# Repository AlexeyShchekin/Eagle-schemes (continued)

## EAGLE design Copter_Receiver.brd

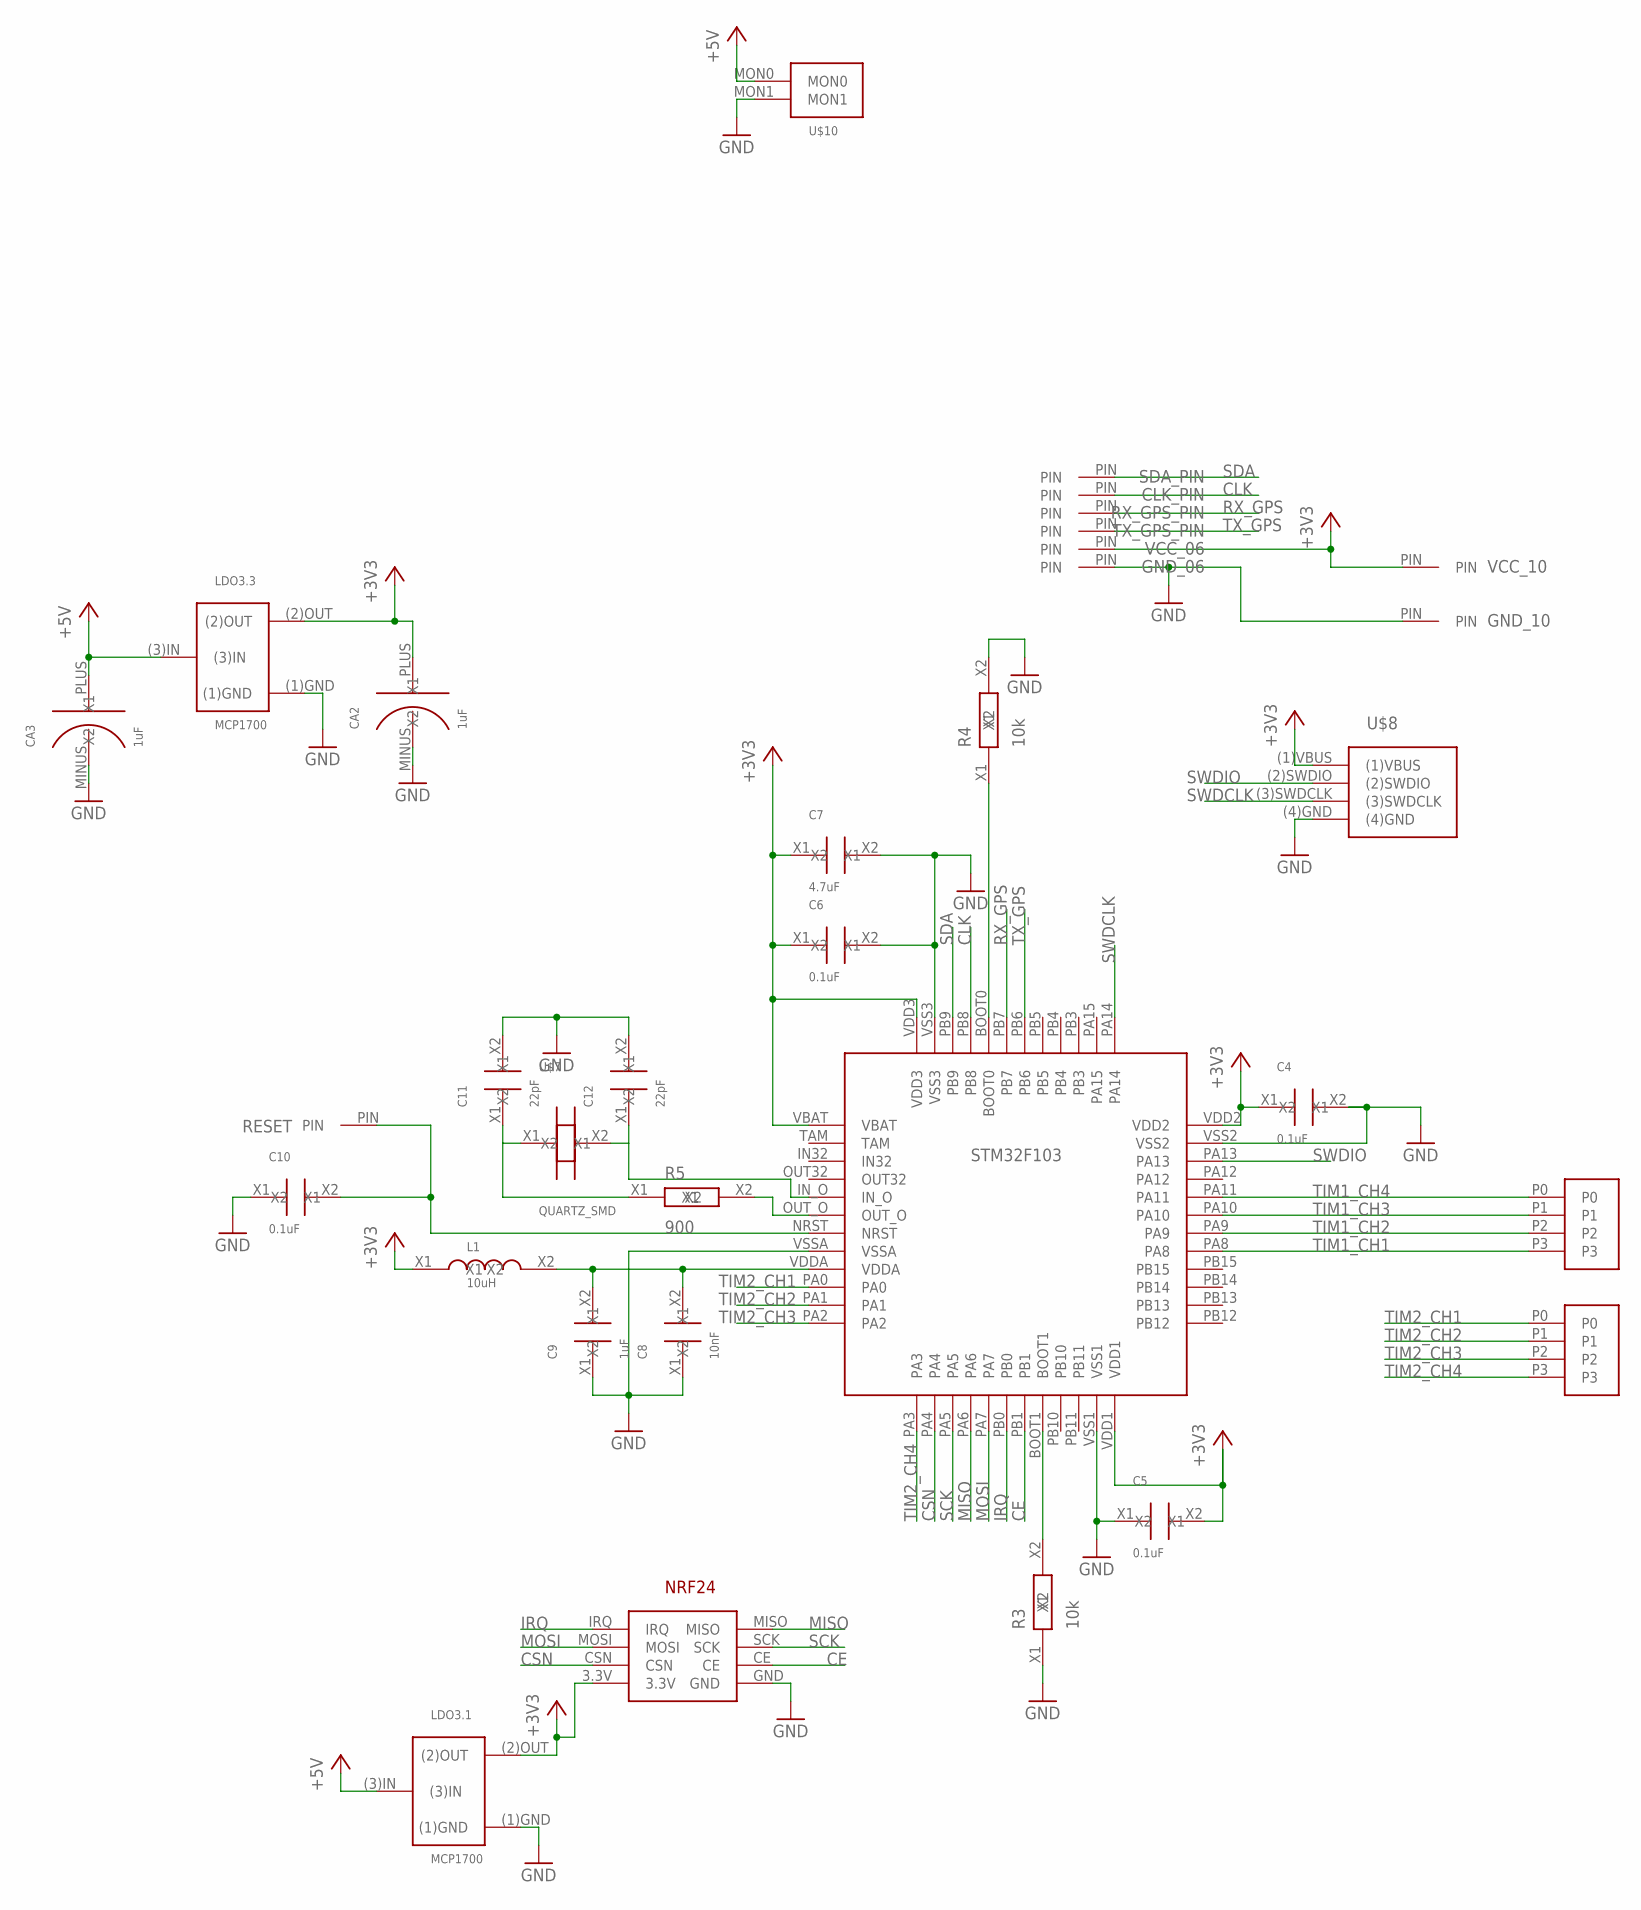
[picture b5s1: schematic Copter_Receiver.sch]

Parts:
C4, C5, C6, C10: 0.1uF; SMD_2.1X1.25
C7: 4.7uF; SMD_2.1X1.25
C8: 10nF; SMD_2.1X1.25
C9: 1uF; SMD_2.1X1.25
C11, C12: 22pF; SMD_2.1X1.25
CA2, CA3: 1uF; C_SMD_TA_A
CLK_PIN: PIN_06
GND_06: PIN_06
GND_10: PIN
L1: 10uH; SMD_2.1X1.25
LDO3.1, LDO3.3: MCP1700
R3, R4: 10k; SMD_2.1X1.25
R5: 900; SMD_2.1X1.25
RESET: PIN
RX_GPS_PIN: PIN_06
SDA_PIN: PIN_06
STM32F103: STM32F103CBT6
TX_GPS_PIN: PIN_06
U$1, U$3: 4PIN
U$2: NRF24_PLUG
U$7: QUARTZ_SMD
U$8: SWD
U$10: MON2PIN
VCC_06: PIN_06
VCC_10: PIN

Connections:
+3V3: C4.X1, C5.X2, C6.X1, C7.X1, CA2.PLUS (X2), L1.X1, LDO3.1.(2)OUT, LDO3.3.(2)OUT, STM32F103.VBAT, STM32F103.VDD1, STM32F103.VDD2, STM32F103.VDD3, U$2.3.3V, U$8.(1)VBUS, VCC_06.PIN, VCC_10.PIN
+5V: CA3.PLUS (X2), LDO3.1.(3)IN, LDO3.3.(3)IN, U$10.MON0
CE: STM32F103.PB1, U$2.CE
CLK: CLK_PIN.PIN, STM32F103.PB8
CSN: STM32F103.PA4, U$2.CSN
GND: C4.X2, C5.X1, C6.X2, C7.X2, C8.X1, C9.X1, C10.X1, C11.X2, C12.X2, CA2.MINUS (X1), CA3.MINUS (X1), GND_06.PIN, GND_10.PIN, LDO3.1.(1)GND, LDO3.3.(1)GND, R3.X1, R4.X2, STM32F103.VSS1, STM32F103.VSS2, STM32F103.VSS3, STM32F103.VSSA, U$2.GND, U$8.(4)GND, U$10.MON1
IRQ: STM32F103.PB0, U$2.IRQ
MISO: STM32F103.PA6, U$2.MISO
MOSI: STM32F103.PA7, U$2.MOSI
unnamed: R3.X2, STM32F103.BOOT1
unnamed: R4.X1, STM32F103.BOOT0
unnamed: R5.X2, STM32F103.OUT_O
unnamed: C11.X1, R5.X1, U$7.X1
unnamed: C12.X1, STM32F103.IN_O, U$7.X2
unnamed: C8.X2, C9.X2, L1.X2, STM32F103.VDDA
unnamed: C10.X2, RESET.PIN, STM32F103.NRST
RX_GPS: RX_GPS_PIN.PIN, STM32F103.PB7
SCK: STM32F103.PA5, U$2.SCK
SDA: SDA_PIN.PIN, STM32F103.PB9
SWDCLK: STM32F103.PA14, U$8.(3)SWDCLK
SWDIO: STM32F103.PA13, U$8.(2)SWDIO
TIM1_CH1: STM32F103.PA8, U$1.P3
TIM1_CH2: STM32F103.PA9, U$1.P2
TIM1_CH3: STM32F103.PA10, U$1.P1
TIM1_CH4: STM32F103.PA11, U$1.P0
TIM2_CH1: STM32F103.PA0, U$3.P0
TIM2_CH2: STM32F103.PA1, U$3.P1
TIM2_CH3: STM32F103.PA2, U$3.P2
TIM2_CH4: STM32F103.PA3, U$3.P3
TX_GPS: STM32F103.PB6, TX_GPS_PIN.PIN

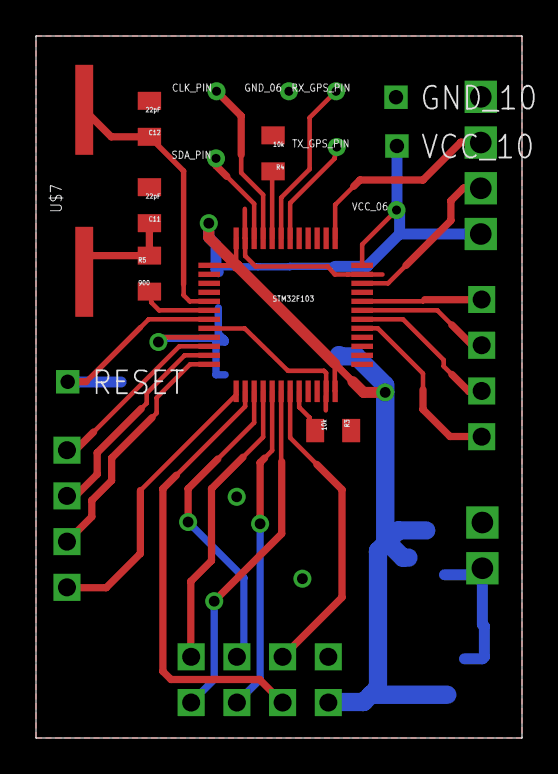
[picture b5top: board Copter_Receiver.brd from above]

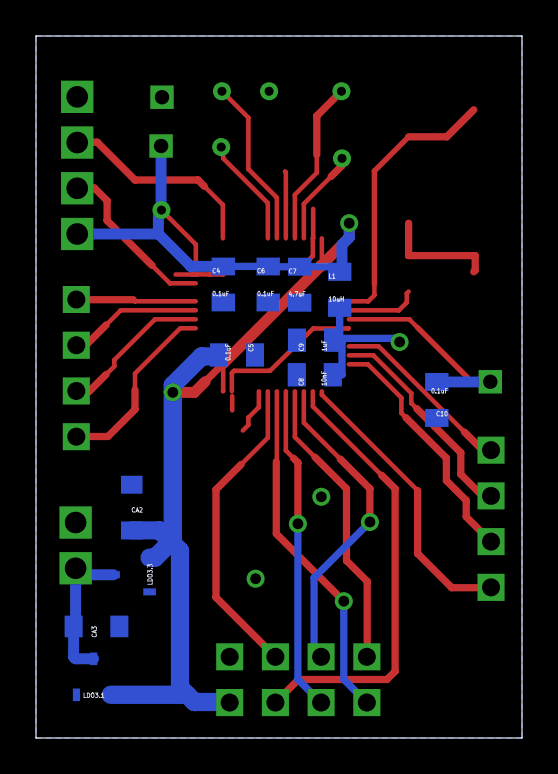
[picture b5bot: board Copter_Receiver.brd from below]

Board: 2 copper layers, 27.0 x 39.0 mm, 33 parts (12 on the bottom side), 30 nets.

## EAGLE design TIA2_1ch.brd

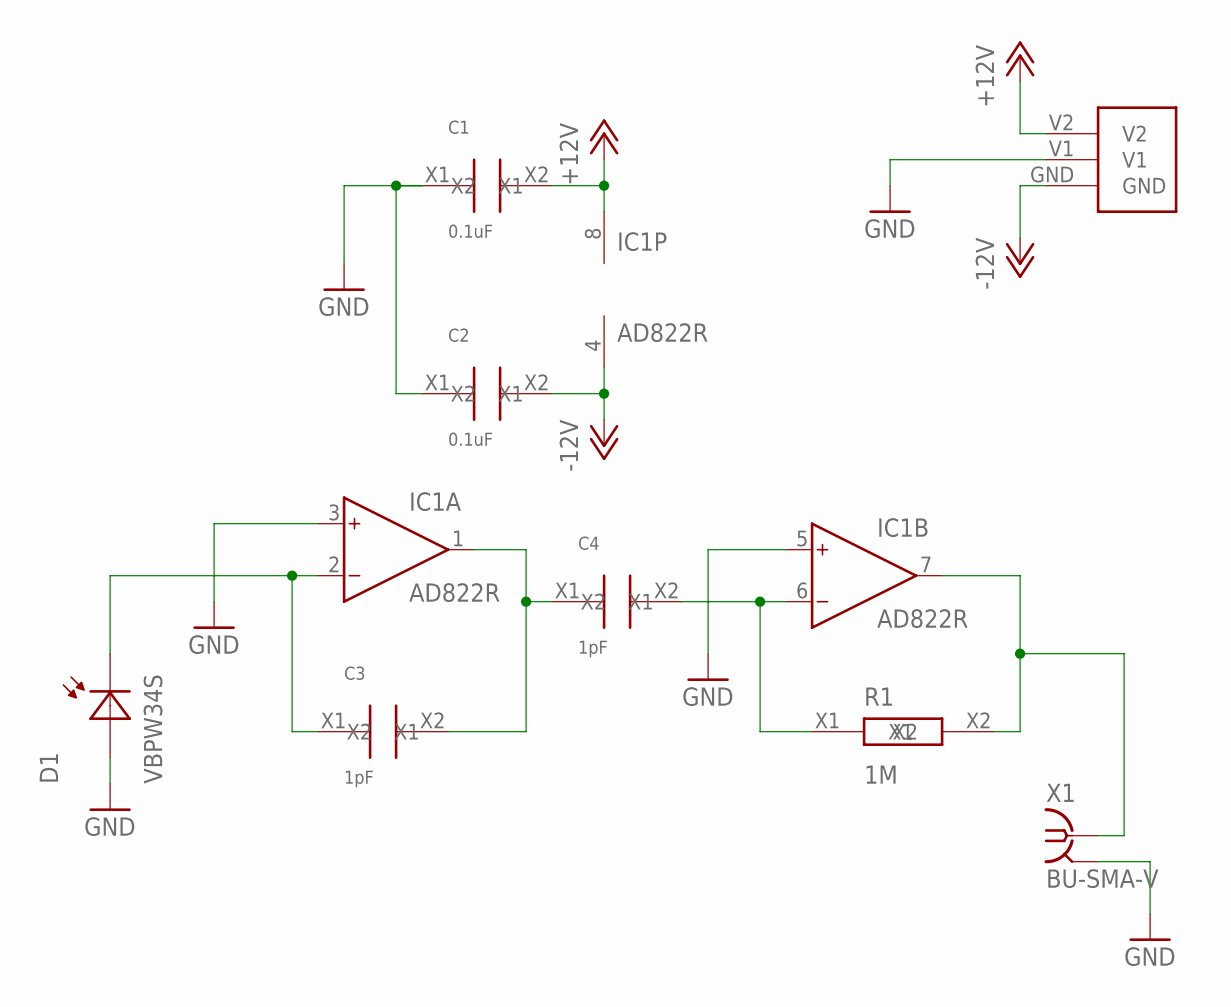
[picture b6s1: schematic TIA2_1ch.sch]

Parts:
C1, C2: 0.1uF; SMD_2.1X1.25
C3, C4: 1pF; SMD_2.1X1.25
D1: VBPW34S; SOD6439X130N
IC1: AD822R; SO8
R1: 1M; SMD_2.1X1.25
U$1: BAT3_PLUG
X1: BU-SMA-V

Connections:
+12V: C1.X2, IC1.8 (V+), U$1.V2
-12V: C2.X2, IC1.4 (V-), U$1.GND
GND: C1.X1, C2.X1, D1.A, IC1.3 (IN+), IC1.5 (IN+), U$1.V1, X1.2, X1.3 (2), X1.4 (2), X1.5 (2)
unnamed: C3.X1, D1.C, IC1.2 (IN-)
unnamed: C3.X2, C4.X1, IC1.1 (OUT)
unnamed: C4.X2, IC1.6 (IN-), R1.X1
unnamed: IC1.7 (OUT), R1.X2, X1.1

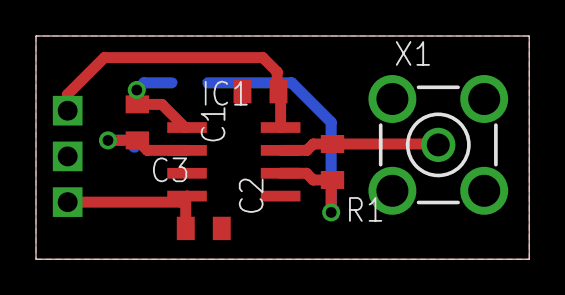
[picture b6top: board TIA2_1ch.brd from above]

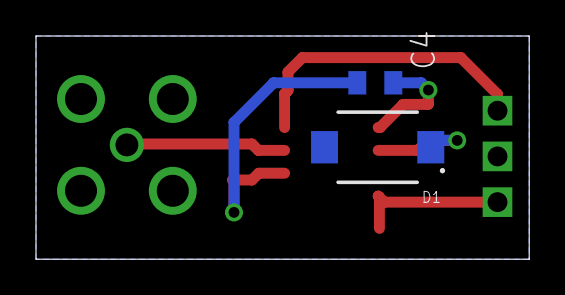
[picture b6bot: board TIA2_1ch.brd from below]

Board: 2 copper layers, 27.4 x 12.4 mm, 9 parts (2 on the bottom side), 7 nets.

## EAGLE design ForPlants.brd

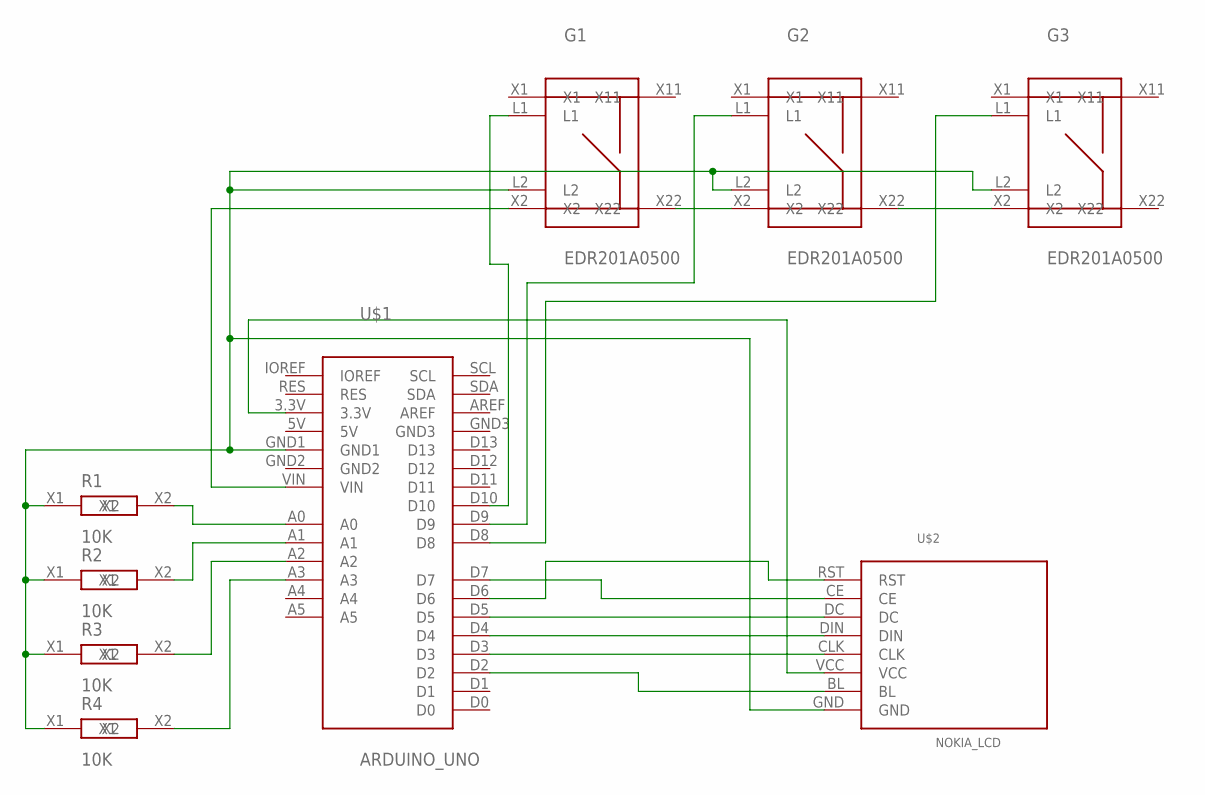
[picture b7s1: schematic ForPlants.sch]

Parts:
G1, G2, G3: EDR201A0500
R1, R2, R3, R4: 10K; SMD_2.1X1.25
U$1: ARDUINO_UNO
U$2: NOKIA_LCD

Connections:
unnamed: U$1.D7, U$2.CE
unnamed: U$1.D6, U$2.RST
unnamed: U$1.D5, U$2.DC
unnamed: U$1.D4, U$2.DIN
unnamed: U$1.D3, U$2.CLK
unnamed: U$1.D2, U$2.BL
unnamed: U$1.3.3V, U$2.VCC
unnamed: R1.X2, U$1.A0
unnamed: R2.X2, U$1.A1
unnamed: R3.X2, U$1.A2
unnamed: R4.X2, U$1.A3
unnamed: G1.L2, G2.L2, G3.L2, R1.X1, R2.X1, R3.X1, R4.X1, U$1.GND1, U$2.GND
unnamed: G1.X2, U$1.VIN
unnamed: G1.X22, G2.X2
unnamed: G2.X22, G3.X2
unnamed: G1.L1, U$1.D10
unnamed: G2.L1, U$1.D9
unnamed: G3.L1, U$1.D8

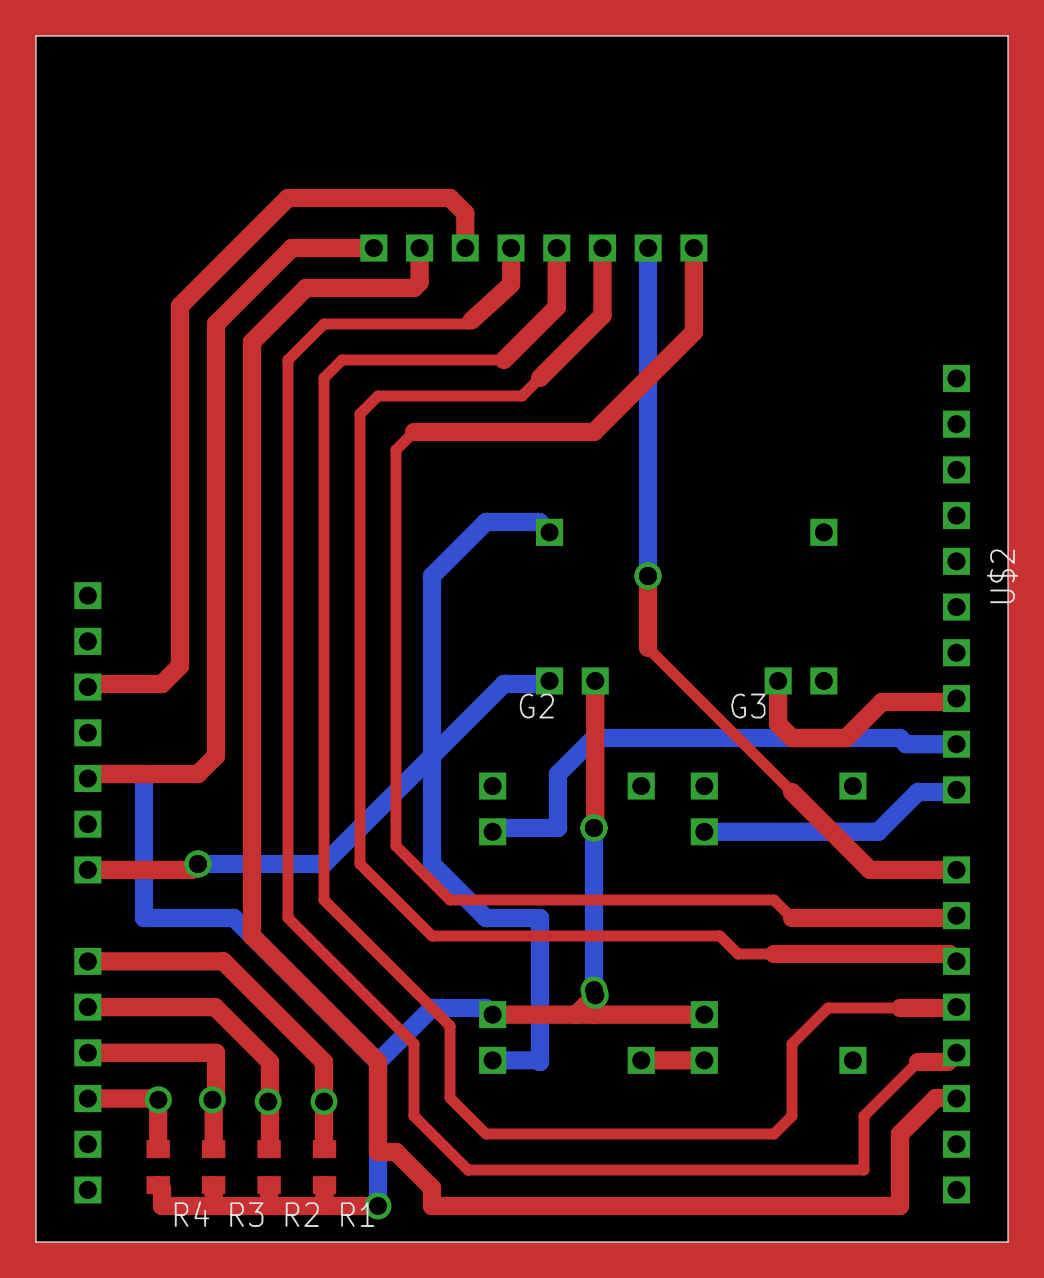
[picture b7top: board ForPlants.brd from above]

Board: 2 copper layers, 54.0 x 67.0 mm, 9 parts (1 on the bottom side), 18 nets.

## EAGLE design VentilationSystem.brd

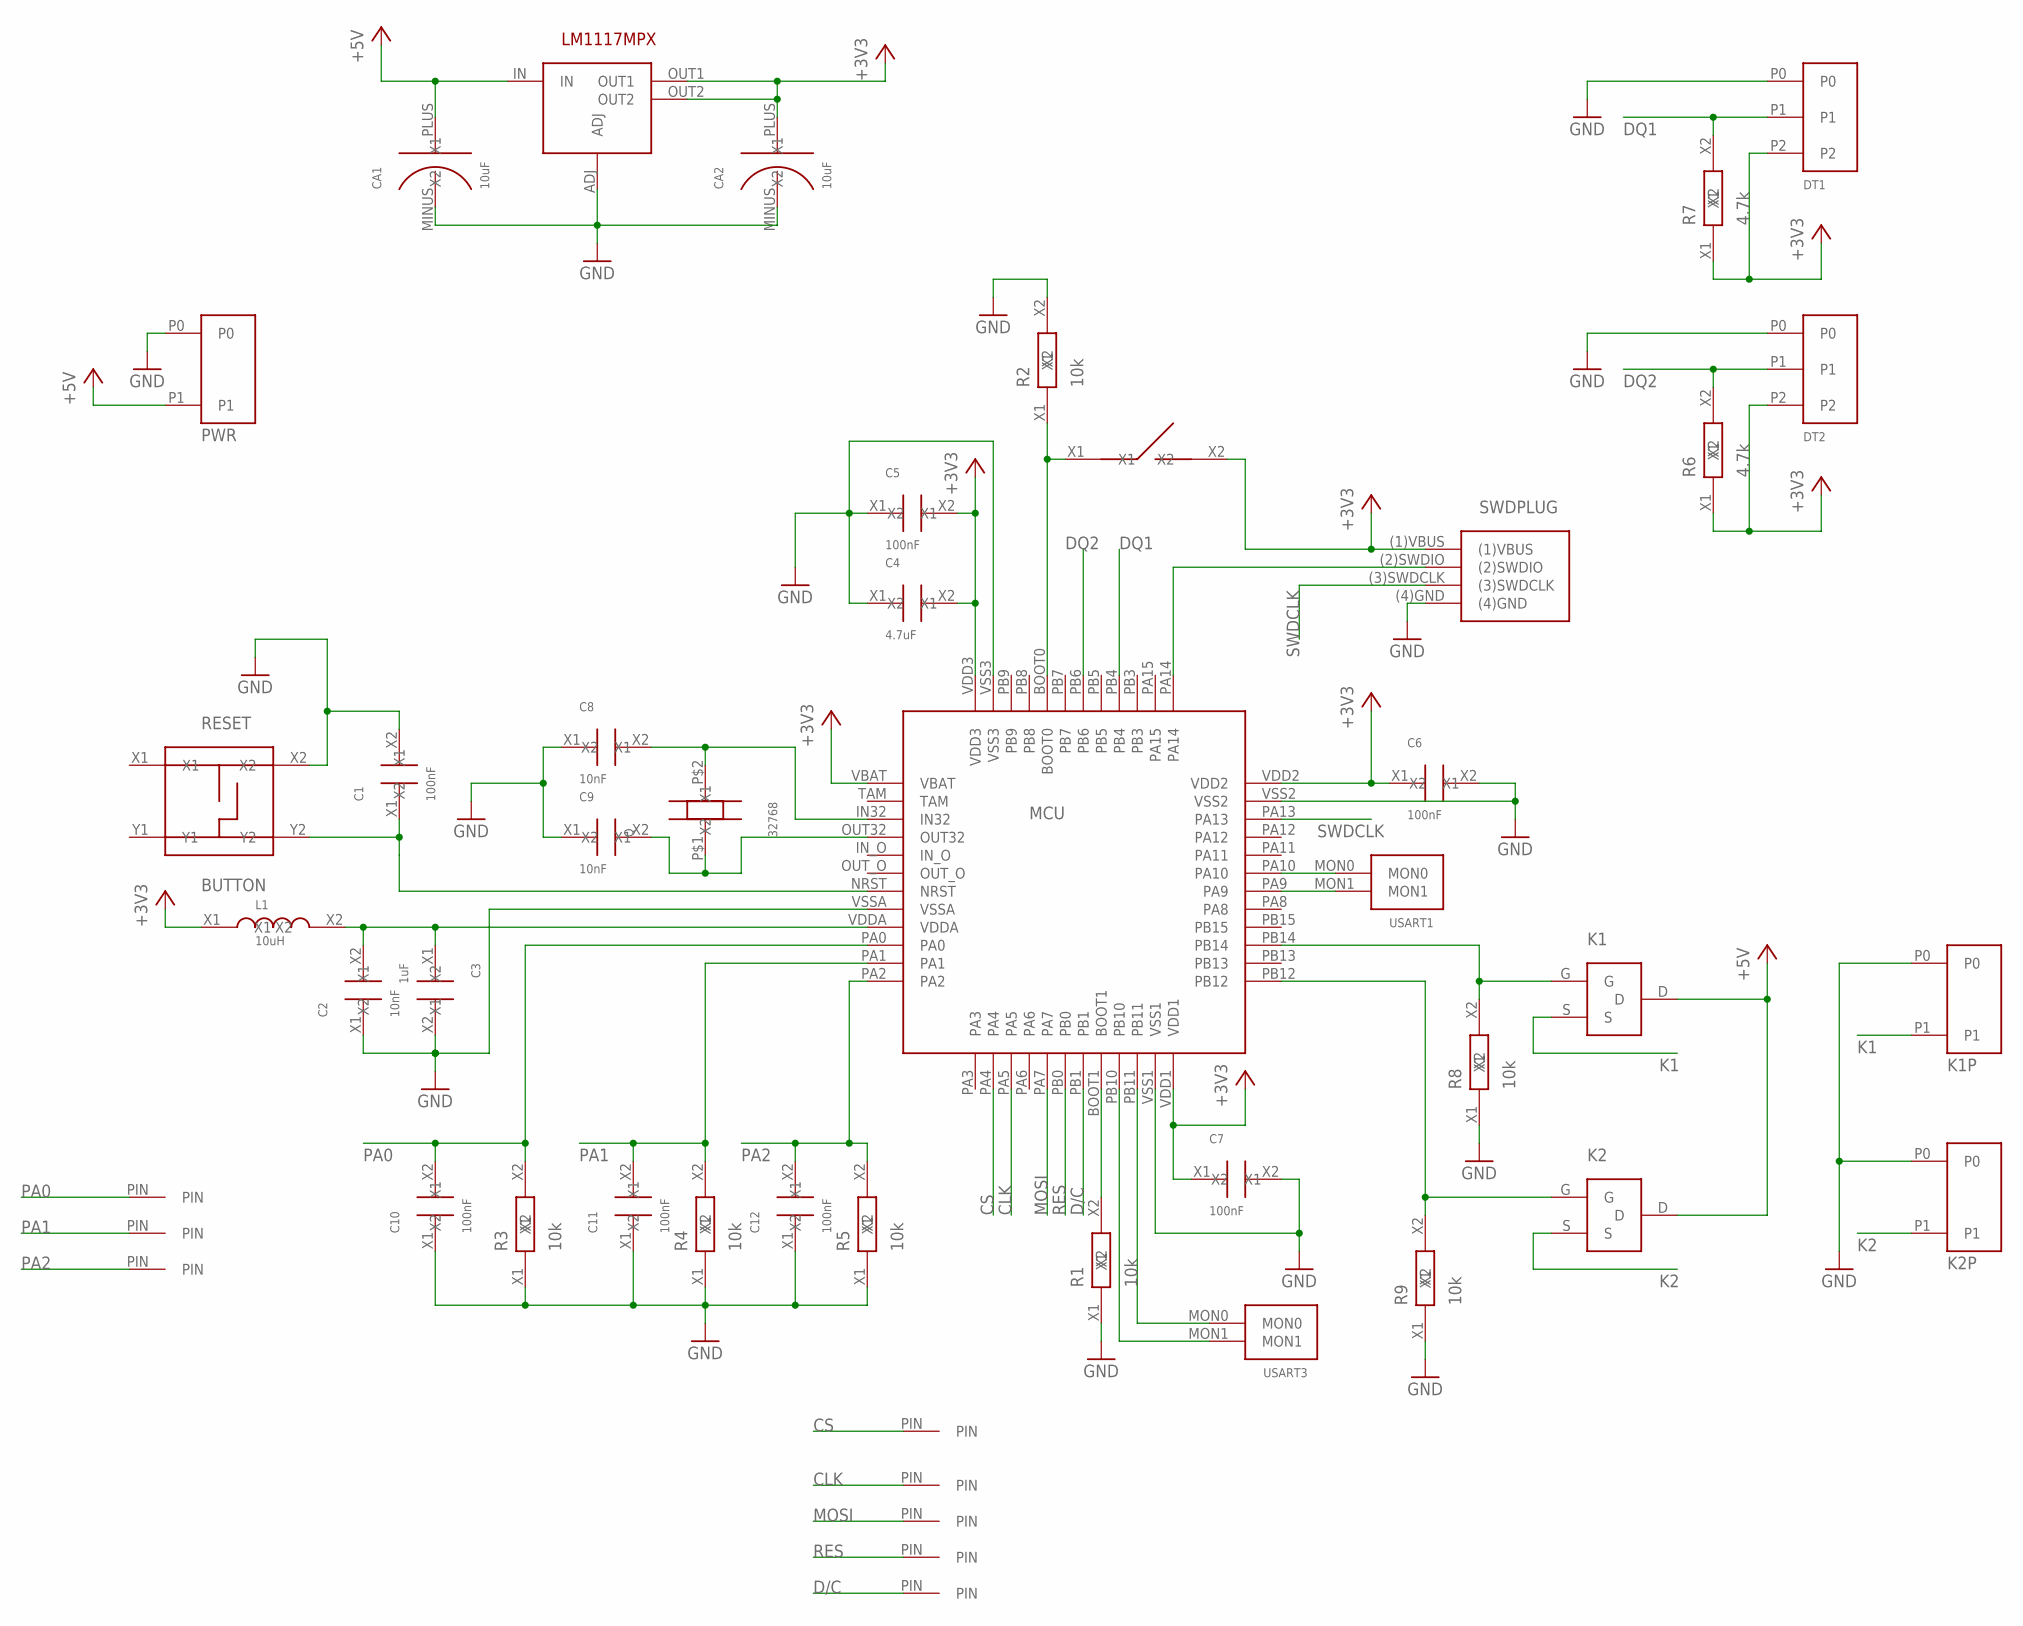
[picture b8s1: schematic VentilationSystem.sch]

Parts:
C1, C5, C6, C7, C10, C11, C12: 100nF; SMD_2.1X1.25
C2, C8, C9: 10nF; SMD_2.1X1.25
C3: 1uF; SMD_2.1X1.25
C4: 4.7uF; SMD_2.1X1.25
CA1, CA2: 10uF; C_SMD_TA_A
CLKPIN: PIN_1
CSPIN: PIN_1
D/CPIN: PIN_1
DT1, DT2: RAIL_3
K1, K2: IRFML8244TRPBF
K1P, K2P: RAIL_2
L1: 10uH; SMD_2.1X1.25
MCU: STM32F103CBT6
MOSIPIN: PIN_1
PA0PIN, PA1PIN, PA2PIN: PIN_1
PWR: RAIL_2
Q: 32768; QUARTZ_CYL
R1, R2, R3, R4, R5, R8, R9: 10k; SMD_2.1X1.25
R6, R7: 4.7k; SMD_2.1X1.25
RESET: BUTTON
RESPIN: PIN_1
SWDPLUG: SWD
U$3: DIP_1
U$4: LM1117MPX-ADJ
USART1, USART3: MON2PIN

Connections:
+3V3: C4.X2, C5.X2, C6.X1, C7.X1, CA2.PLUS (X2), DT1.P2, DT2.P2, L1.X1, MCU.VBAT, MCU.VDD1, MCU.VDD2, MCU.VDD3, R6.X1, R7.X1, SWDPLUG.(1)VBUS, U$3.X2, U$4.OUT1, U$4.OUT2
+5V: CA1.PLUS (X2), K1.D, K2.D, PWR.P1, U$4.IN
CLK: CLKPIN.PIN, MCU.PA5
CS: CSPIN.PIN, MCU.PA4
D/C: D/CPIN.PIN, MCU.PB1
DQ1: DT1.P1, MCU.PB4, R7.X2
DQ2: DT2.P1, MCU.PB6, R6.X2
GND: C1.X2, C2.X1, C3.X2, C4.X1, C5.X1, C6.X2, C7.X2, C8.X1, C9.X1, C10.X1, C11.X1, C12.X1, CA1.MINUS (X1), CA2.MINUS (X1), DT1.P0, DT2.P0, K1P.P0, K2P.P0, MCU.VSS1, MCU.VSS2, MCU.VSS3, MCU.VSSA, PWR.P0, R1.X1, R2.X2, R3.X1, R4.X1, R5.X1, R8.X1, R9.X1, RESET.X2, SWDPLUG.(4)GND, U$4.ADJ
K1: K1.S, K1P.P1
K2: K2.S, K2P.P1
MOSI: MCU.PA7, MOSIPIN.PIN
unnamed: C2.X2, C3.X1, L1.X2, MCU.VDDA
unnamed: MCU.BOOT0, R2.X1, U$3.X1
unnamed: MCU.BOOT1, R1.X2
unnamed: C1.X1, MCU.NRST, RESET.Y2
unnamed: MCU.PA10, USART1.MON0
unnamed: MCU.PA14, SWDPLUG.(2)SWDIO
unnamed: MCU.PA9, USART1.MON1
unnamed: C9.X2, MCU.OUT32, Q.P$1 (X1)
unnamed: C8.X2, MCU.IN32, Q.P$2 (X2)
unnamed: K1.G, MCU.PB14, R8.X2
unnamed: K2.G, MCU.PB12, R9.X2
unnamed: MCU.PB11, USART3.MON0
unnamed: MCU.PB10, USART3.MON1
PA0: C10.X2, MCU.PA0, PA0PIN.PIN, R3.X2
PA1: C11.X2, MCU.PA1, PA1PIN.PIN, R4.X2
PA2: C12.X2, MCU.PA2, PA2PIN.PIN, R5.X2
RES: MCU.PB0, RESPIN.PIN
SWDCLK: MCU.PA13, SWDPLUG.(3)SWDCLK

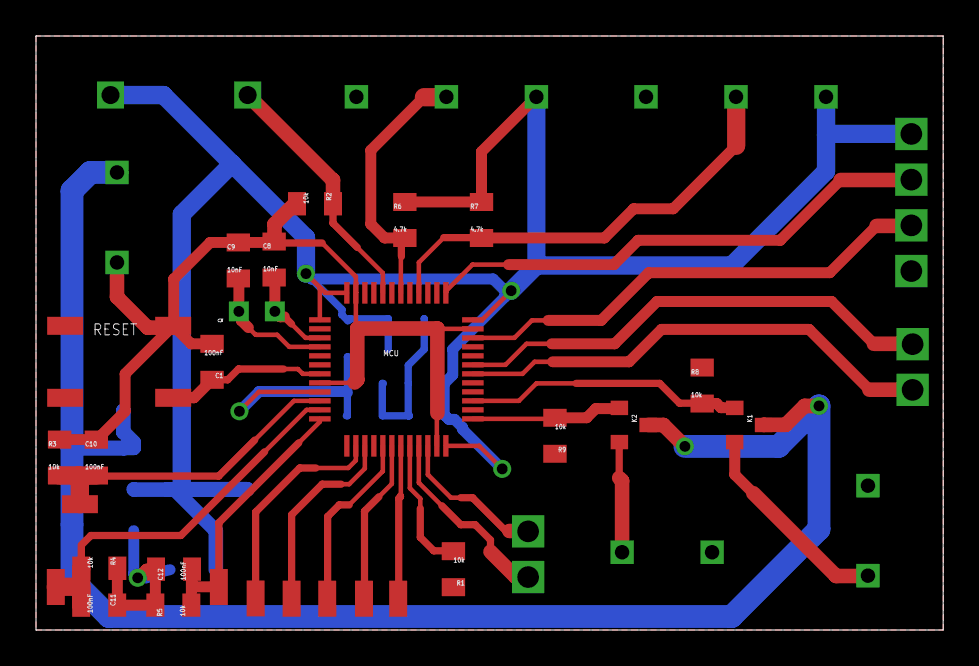
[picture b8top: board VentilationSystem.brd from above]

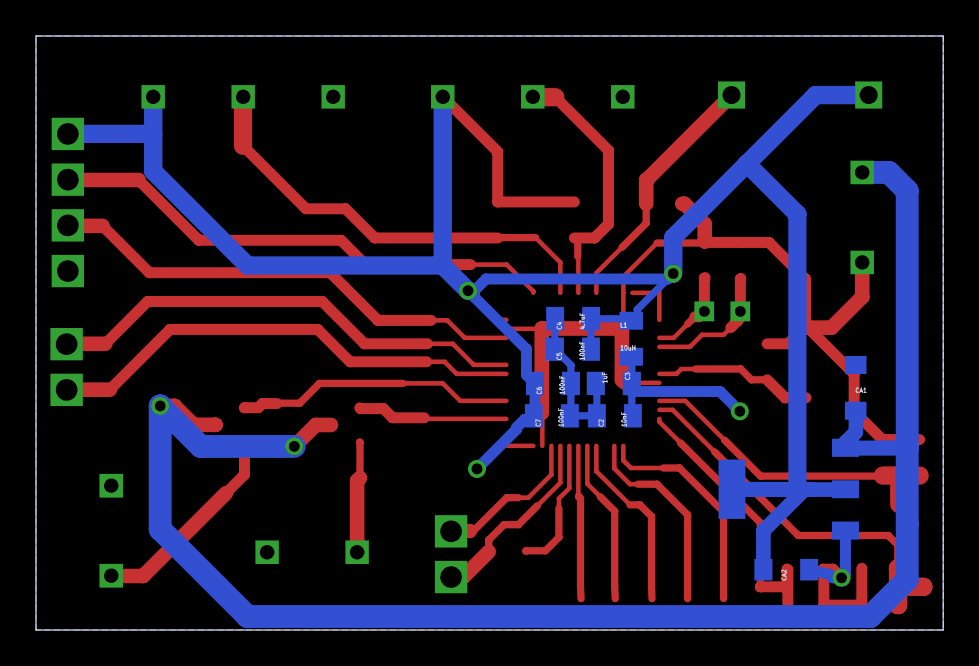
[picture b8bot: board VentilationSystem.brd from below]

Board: 2 copper layers, 50.4 x 33.0 mm, 47 parts (10 on the bottom side), 29 nets.

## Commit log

2018-06-02 .gitignore
2018-11-03 TIA added
2019-03-29 Transmitter finished
